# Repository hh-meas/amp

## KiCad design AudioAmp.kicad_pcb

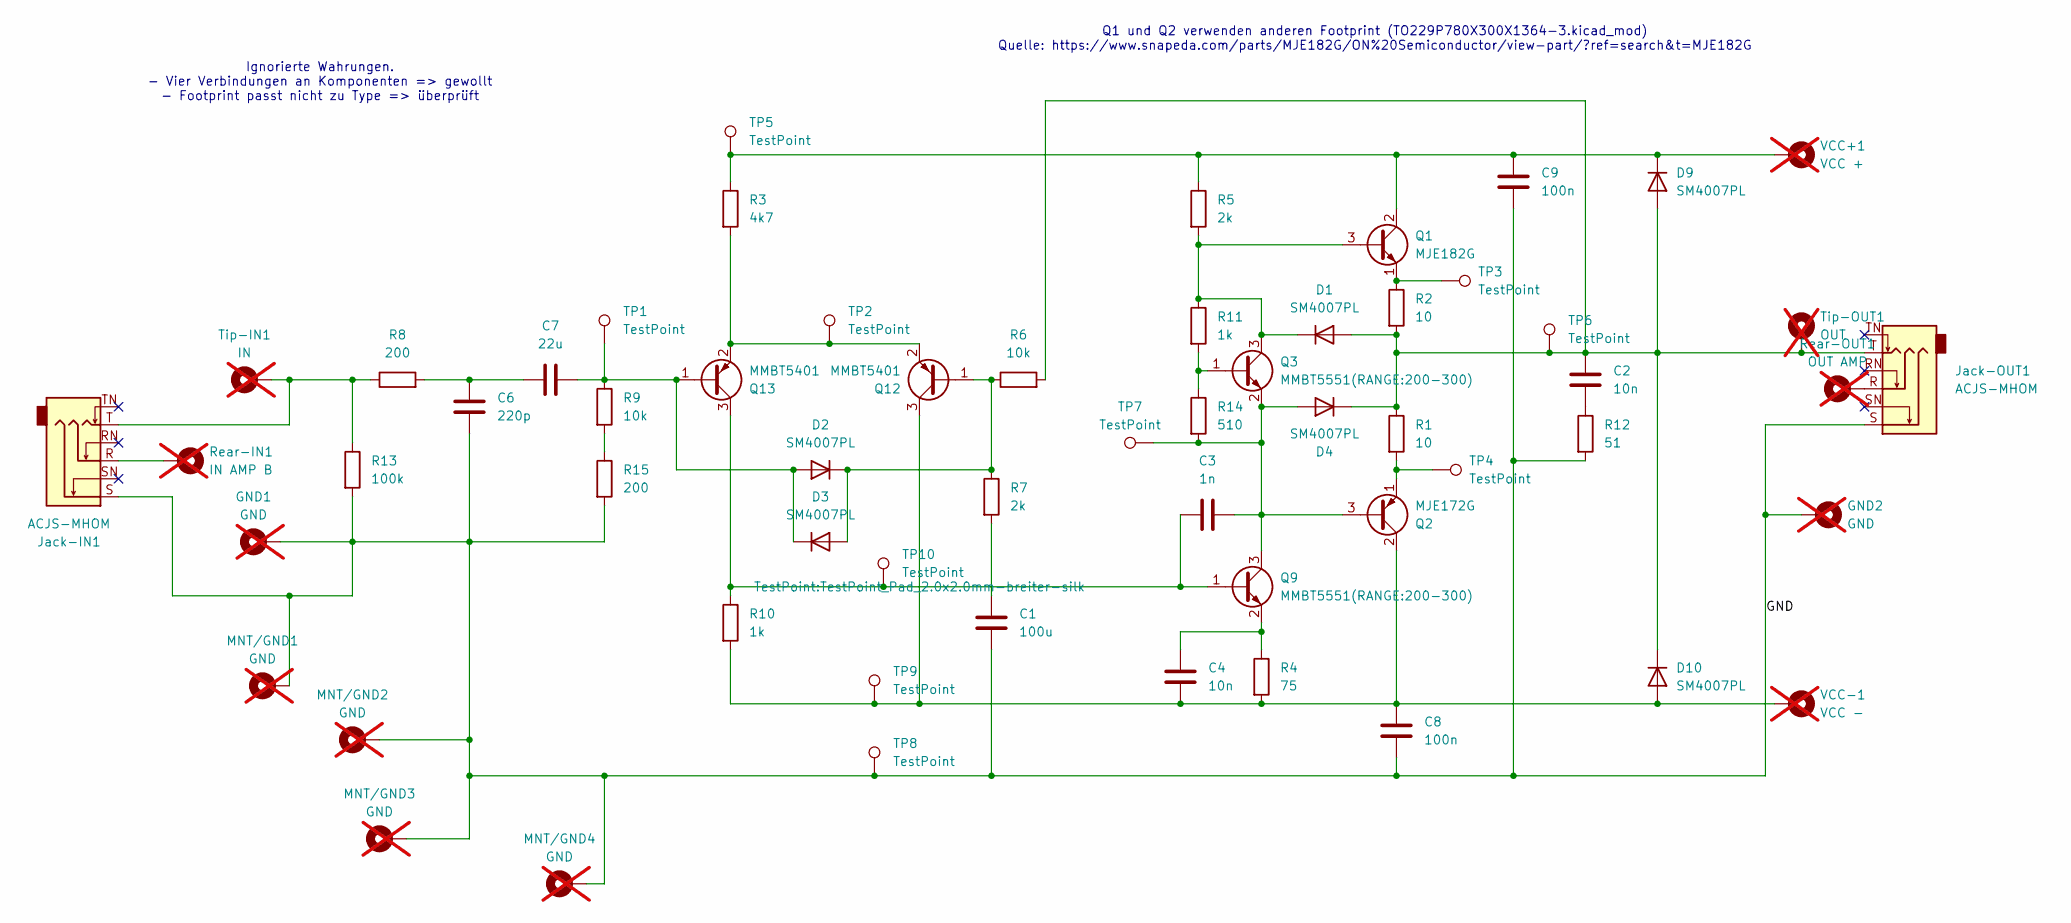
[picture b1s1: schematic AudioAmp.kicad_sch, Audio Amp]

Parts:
C1: 100u; C_1206_3216Metric; MPN C15008
C2, C4: 10n; C_0805_2012Metric; MPN C1710
C3: 1n; C_0603_1608Metric; MPN C1588
C6: 220p; C_0603_1608Metric; MPN C1603
C7: 22u; C_1206_3216Metric; MPN C12891
C8, C9: 100n; C_0603_1608Metric; MPN C14663
D1, D2, D3, D4, D9, D10: SM4007PL; D_SOD-123F; MPN C64898
GND1, GND2: GND; MountingHole_2.5mm_Pad; not fitted
Jack-IN1: ACJS-MHOM; Jack_6.35mm_Neutrik_NRJ6HM-1_Horizontal; MPN C4991596
Jack-OUT1: ACJS-MHOM; Jack_6.35mm_Neutrik_NRJ6HM-1_Horizontal; MPN C4991596
MNT/GND1, MNT/GND2, MNT/GND3, MNT/GND4: GND; MountingHole_2.5mm_Pad; not fitted
Q1: MJE182G; TO229P780X300X1364-3; MPN C27681
Q2: MJE172G; TO229P780X300X1364-3; MPN C27682
Q3, Q9: MMBT5551(RANGE:200-300); SOT-23; MPN C2145
Q12, Q13: MMBT5401; SOT-23; MPN C8326
R1, R2: 10; R_1206_3216Metric; MPN C17903
R3: 4k7; R_1206_3216Metric; MPN C17936
R4: 75; R_0603_1608Metric; MPN C4275
R5, R7: 2k; R_1206_3216Metric; MPN C17944
R6, R9: 10k; R_1206_3216Metric; MPN C17902
R8, R15: 200; R_0805_2012Metric; MPN C17540
R10, R11: 1k; R_1206_3216Metric; MPN C4410
R12: 51; R_0805_2012Metric; MPN C17738
R13: 100k; R_1206_3216Metric; MPN C17900
R14: 510; R_0805_2012Metric; MPN C17734
Rear-IN1: IN AMP B; MountingHole_2.5mm_Pad; not fitted
Rear-OUT1: OUT AMP; MountingHole_2.5mm_Pad; not fitted
TP1, TP2, TP3, TP4, TP5, TP6, TP7, TP8, TP9, TP10: TestPoint; TestPoint_Pad_2.0x2.0mm-breiter-silk
Tip-IN1: IN; MountingHole_2.5mm_Pad; not fitted
Tip-OUT1: OUT; MountingHole_2.5mm_Pad; not fitted
VCC+1: VCC +; MountingHole_2.5mm_Pad; not fitted
VCC-1: VCC -; MountingHole_2.5mm_Pad; not fitted

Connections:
/GND: C1.2, C6.2, C8.2, C9.2, GND1.1, GND2.1, Jack-IN1.S, Jack-OUT1.S, MNT/GND1.1, MNT/GND2.1, MNT/GND3.1, MNT/GND4.1, R12.2, R13.2, R15.2, TP8.1
unnamed: C1.1, R7.2
unnamed: C2.2, R12.1
unnamed: C6.1, C7.1, R8.2
unnamed: C2.1, D1.2 (A), D4.1 (K), D9.2 (A), D10.1 (K), Jack-OUT1.T, R1.1, R2.2, R6.2, TP6.1, Tip-OUT1.1
unnamed: D1.1 (K), Q1.3 (B), Q3.3 (C), R5.2, R11.1
unnamed: C7.2, D2.2 (A), D3.1 (K), Q13.1 (B), R9.1, TP1.1
unnamed: D2.1 (K), D3.2 (A), Q12.1 (B), R6.1, R7.1
unnamed: C3.2, D4.2 (A), Q2.3 (B), Q3.2 (E), Q9.3 (C), R14.2, TP7.1
unnamed: C9.1, D9.1 (K), Q1.2 (C), R3.1, R5.1, TP5.1, VCC+1.1
unnamed: C4.2, C8.1, D10.2 (A), Q2.2 (C), Q12.3 (C), R4.2, R10.2, TP9.1, VCC-1.1
unnamed: Jack-IN1.R, Rear-IN1.1
unnamed: Jack-IN1.T, R8.1, R13.1, Tip-IN1.1
unnamed: Jack-OUT1.R, Rear-OUT1.1
unnamed: Q1.1 (E), R2.1, TP3.1
unnamed: Q2.1 (E), R1.2, TP4.1
unnamed: Q3.1 (B), R11.2, R14.1
unnamed: C4.1, Q9.2 (E), R4.1
unnamed: Q12.2 (E), Q13.2 (E), R3.2, TP2.1
unnamed: C3.1, Q9.1 (B), Q13.3 (C), R10.1, TP10.1
unnamed: R9.2, R15.1

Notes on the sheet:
Ignorierte Wahrungen. - Vier Verbindungen an Komponenten => gewollt - Footprint passt nicht zu Type => überprüft
Q1 und Q2 verwenden anderen Footprint (TO229P780X300X1364-3.kicad_mod) Quelle: https://www.snapeda.com/parts/MJE182G/ON%20Semiconductor/view-part/?ref=search&t=MJE182G

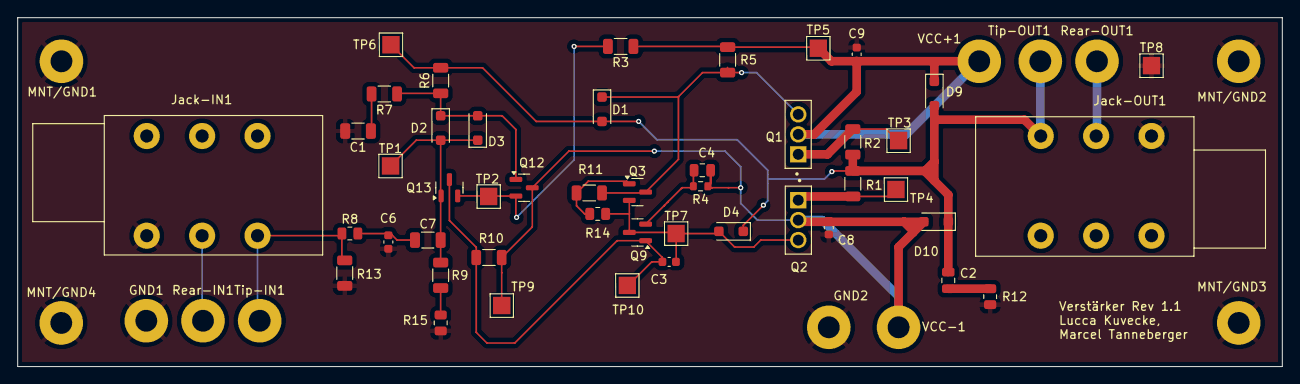
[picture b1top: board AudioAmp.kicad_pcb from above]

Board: 2 copper layers, 145.0 x 40.0 mm, 59 parts (0 on the bottom side), 21 nets.

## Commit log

2025-04-22 Create .gitignore kicad
2025-04-29 Init
    init 29.04
2025-04-29 change: Testpoints
    Testpoint footprints
2025-04-29 ignores hingefügt
2025-05-04 Add: DRU / JLS Design Rules
2025-05-04 CHA: Footprint von Pin auf Fläche
2025-05-04 Add: PCB 1.1
2025-05-04 ADD: Footprint Q1/Q2
2025-05-04 Test
2025-05-05 PCB fertig gemacht.
2025-05-05 CHA: Leitung zu Hochstrom erhöht
2025-05-05 Neues GND Netz gesetz und angeschlossen, Planinen rev hinzugefügt
2025-05-05 Add: Label GND
2025-05-06 CHA: Projektdaten ergänzt
2025-05-06 CHA: Testpin zu Points
2025-05-06 CHA: PCB Testpin zu point, refill GND
2025-05-06 CHA: H6 raus
2025-05-06 CHA: TP8 changed
2025-05-06 CHA: MPN bei den Testpoints raus
2025-05-06 CHA: Tp auf 2mm
2025-05-06 CHA: PCB Testpad breiter
2025-05-06 CHA: Testpoints mit breiterem SILK
2025-05-06 CHA: Projekt - alle warn, TP10 Überschneidung
2025-05-06 CHA: Insel ohne Füllung gefüllt, dazu via gesetz
2025-05-06 ^CHA: Verbesserungen Füll GND
2025-05-06 ADD: breiter Testpad
2025-05-06 TP6 Schrift verschoben
2025-05-06 Beshriftung ausgerichtet
2025-05-06 CHA: Testpads, leitungsänderungen
2025-05-06 TP Beschriftung verschoben
2025-05-06 Loses Leiterende entfern
2025-05-06 Beschriftung platine im Silklayer + Schriftdicke auf 1.5 mm
2025-05-06 CHA: Silkscreen Beschriftungen nun lesbar statt nummeriert
2025-05-06 CHA: Optimierungen in Leiterbahnen
2025-05-07 CHA: Syncronität SHA / PCB
2025-05-09 ADD: Files from JLC Production Plugin
2025-06-03 CHA: rev 1.2 - der C3 liegt falsch
